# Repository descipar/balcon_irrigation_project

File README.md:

# Balcony Irrigation Project

Automatische Balkonbewässerung: kapazitive Bodenfeuchtesensoren messen die Erde,
kleine 5V-Pumpen gießen bei Bedarf nach.

> **Status:** Version 1 (Arduino Uno, Breadboard) hat funktioniert, hatte aber Bugs
> und war wenig "intelligent". Version 2 (ESP32 + eigene Platine + ESPHome/Home Assistant)
> ist in Planung – siehe [`docs/`](docs/).

## Repository-Struktur

| Pfad | Inhalt |
|---|---|
| `vscode_workspace/BalconIrrigation/` | **Firmware v1** (PlatformIO, Arduino Uno) – letzte lauffähige Version |
| `arduino_workspace/balcon_irrigation/` | Ältere Arduino-IDE-Version (veraltet, gießt nur Topf 1) |
| `arduino_workspace/GraphicsTestExample/` | u8g2-Beispiel aus einem verworfenen Display-Versuch |
| `fritzing_workspace/` | Schaltung v1 (Fritzing): Uno, 5× Sensor, 5× Pumpe über BC337 + 1N4148 |
| `stl/` | 3D-Druckteile: Filmdosen-Behälter (12/20/47 mm), Deckel, Wasserverteiler |
| `docs/` | Analyse von v1, Hardware-Konzept und PCB-Plan für v2 |

## Version 1 (Arduino Uno)

- 2 von 5 Kanälen aktiv: Sensoren an `A0`/`A1`, Pumpen an Pin `10`/`11`
- Alle 30 s messen; Wert > 350 (= trocken) → Pumpe 3 s an
- Bauen/Flashen mit PlatformIO:
  ```sh
  cd vscode_workspace/BalconIrrigation
  pio run -t upload && pio device monitor
  ```

Bekannte Probleme (Details in [`docs/v1-analysis.md`](docs/v1-analysis.md)):
Überwässerungsgefahr ohne Einsickerzeit, keine Hysterese, keine Erkennung
von Sensorfehlern oder leerem Tank, Messwerte gestört durch Pumpen an der gleichen 5V-Versorgung,
`int`-Überlauf bei Wartezeiten > 32767 ms.

## Version 2 (geplant)

- **ESP32** statt Uno – WLAN, NTP-Zeit, OTA-Updates
- **Eigene Platine**, gefertigt und bestückt bei JLCPCB (KiCad)
- 5 Kanäle, Logic-Level-MOSFETs für 5V-Pumpen, separate Pumpenversorgung
- **ESPHome + Home Assistant** für Logik, Verlauf und Benachrichtigungen

Siehe:
- [`docs/v1-analysis.md`](docs/v1-analysis.md) – Bugs & Schwachstellen von v1
- [`docs/v2-hardware.md`](docs/v2-hardware.md) – ESP32-Konzept, Pumpenansteuerung, Pinbelegung
- [`docs/v2-pcb.md`](docs/v2-pcb.md) – PCB-Plan und Toolchain (KiCad auf `serviceplasma`)

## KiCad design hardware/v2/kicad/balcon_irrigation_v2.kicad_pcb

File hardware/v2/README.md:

# Hardware v2 – Steuerplatine

| Datei | Inhalt |
|---|---|
| `gen_schematic.py` | Erzeugt den Schaltplan (die Schaltung ist in `build()` definiert) |
| `kicad/balcon_irrigation_v2.kicad_sch` | Generierter KiCad-9-Schaltplan (A3, 1 Blatt) |
| `kicad/balcon_irrigation_v2.kicad_pro` | KiCad-Projekt |
| `kicad/balcon_irrigation_v2.pdf` | Schaltplan als PDF |
| `gen_layout.py` | Erzeugt und routet die Platine (Platzierung in `placement()`) |
| `kicad/balcon_irrigation_v2.kicad_pcb` | Platine, 100 × 100 mm, 2 Lagen |
| `kicad/balcon_irrigation_v2_top.pdf` / `_bottom.pdf` | Ober- und Unterseite als PDF |

Der Schaltplan wird **nicht von Hand editiert**, sondern neu generiert:

```sh
python3 gen_schematic.py kicad                                    # braucht KiCad-9-Symbolbibliotheken
kicad-cli sch erc --severity-all kicad/balcon_irrigation_v2.kicad_sch
kicad-cli sch export pdf kicad/balcon_irrigation_v2.kicad_sch
```

Die Bibliotheken liegen standardmäßig unter `/usr/share/kicad`, ein anderer Ort geht über `KICAD_SHARE=...`.
Die UUIDs sind deterministisch, deshalb erzeugt derselbe Code mit denselben Bibliotheken (9.0.2) eine byte-identische Datei.
Die Verbindungen laufen über Netz-Labels und Power-Symbole an jedem Pin, nicht über gezeichnete Leitungen.

## Layout

```sh
python3 gen_layout.py kicad/balcon_irrigation_v2.kicad_sch     # ~2 min, braucht pcbnew + Freerouting
kicad-cli pcb drc --schematic-parity kicad/balcon_irrigation_v2.kicad_pcb
```

Ablauf des Skripts:
1. Netzliste aus dem Schaltplan exportieren.
2. Footprints platzieren.
3. Umriss, Bestückungsdruck und Sperrfläche unter der Antenne anlegen.
4. Leiterbahnen mit Freerouting verlegen.
5. Erst danach die GND-Flächen auf beiden Lagen gießen.

Netzklassen: `Power` (+5V, VIN, PUMPx_N) 0,8 mm, `Ground` 0,5 mm, sonst 0,25 mm.
Freerouting liefert bei jedem Lauf ein etwas anderes Ergebnis.
Das eingecheckte `.kicad_pcb` ist der geprüfte Stand.

Platzierung:
- **Links:** Versorgung (Hohlbuchse, Schraubklemme, Sicherung, Verpolschutz, Elko)
- **Oben:** Sensor-, Tank- und I²C-Buchsen
- **Mitte:** DevKit, Antenne rechts über dem Platinenrand, USB links
- **Unten:** 5 Pumpenklemmen mit Treibern
- **Rechts:** Erweiterungsleiste
- **Ecken:** 4 × M3-Bohrungen

## Schaltung

**Versorgung:** 5 V über Hohlbuchse oder Schraubklemme, dann PTC-Sicherung (2 A),
dann Verpolschutz (AO3401A, P-MOSFET high-side), dann `+5V`.
Dazu ein Pufferelko 1000 µF und 100 nF.
`+5V` speist die Pumpen und den 5V-Pin des DevKits. `+3V3` kommt vom Regler des DevKits.

**ESP32-DevKitC V4:** steckt auf 2× Buchsenleiste 1×19 mit 25,4 mm Reihenabstand.
Die Pinbelegung steht in [`docs/v2-hardware.md`](../../docs/v2-hardware.md).

**Pumpenkanal (5×):**
- GPIO → 100 Ω → Gate AO3400A, mit 10k-Pulldown am Gate
- Low-side-Schaltung
- Schottky SS14 als Freilaufdiode zu `+5V`
- Anschluss über Schraubklemme (`+5V` / `PUMPx_N`)

**Sensorkanal (5×):**
- JST-XH 3-polig (GND / 3V3 / AOUT)
- RC-Tiefpass 1 kΩ + 100 nF vor dem ADC1-Pin

**Peripherie:**
- Tank-Schwimmer (JST-XH 2-polig, 10k-Pull-up, RC-Entprellung) an GPIO39
- I²C (JST-XH 4-polig, GND/3V3/SCL/SDA, 4,7k Pull-ups)
- Status-LED an GPIO27
- Erweiterungsleiste mit GPIO 4/13/16/17
- 4× Montageloch M3

LCSC-Nummern (JLC Basic Parts) sind als Feld `LCSC` hinterlegt.
Für Elko, PTC und Steckverbinder fehlen sie noch.

## Vor dem Layout prüfen

- [ ] **DevKit-Variante:** Reihenabstand und Pinfolge am eigenen Board nachmessen.
  Es gibt viele Klone mit 30 Pins oder anderer Breite.
- [ ] **USB + externe 5 V gleichzeitig:** Prüfen, ob das DevKit eine Diode zwischen USB-5V und dem 5V-Pin hat.
  Sonst beim Flashen über USB das Netzteil abziehen.
- [ ] **Pumpenstrom messen:** Anlauf- und Dauerstrom bestimmen. Davon hängen PTC, Leiterbahnbreite und Netzteil ab.
- [ ] **LCSC-Nummern** und Lagerbestand bei JLCPCB prüfen. Fehlende Teile ergänzen: PTC 1812, Elko, XH-Buchsen, Schraubklemmen.
- [ ] **Sensor-Stecker:** Der DFRobot-Sensor hat am Modul einen PH2.0-Stecker.
  Kabel auf JST-XH umcrimpen oder auf der Platine PH2.0 verwenden.

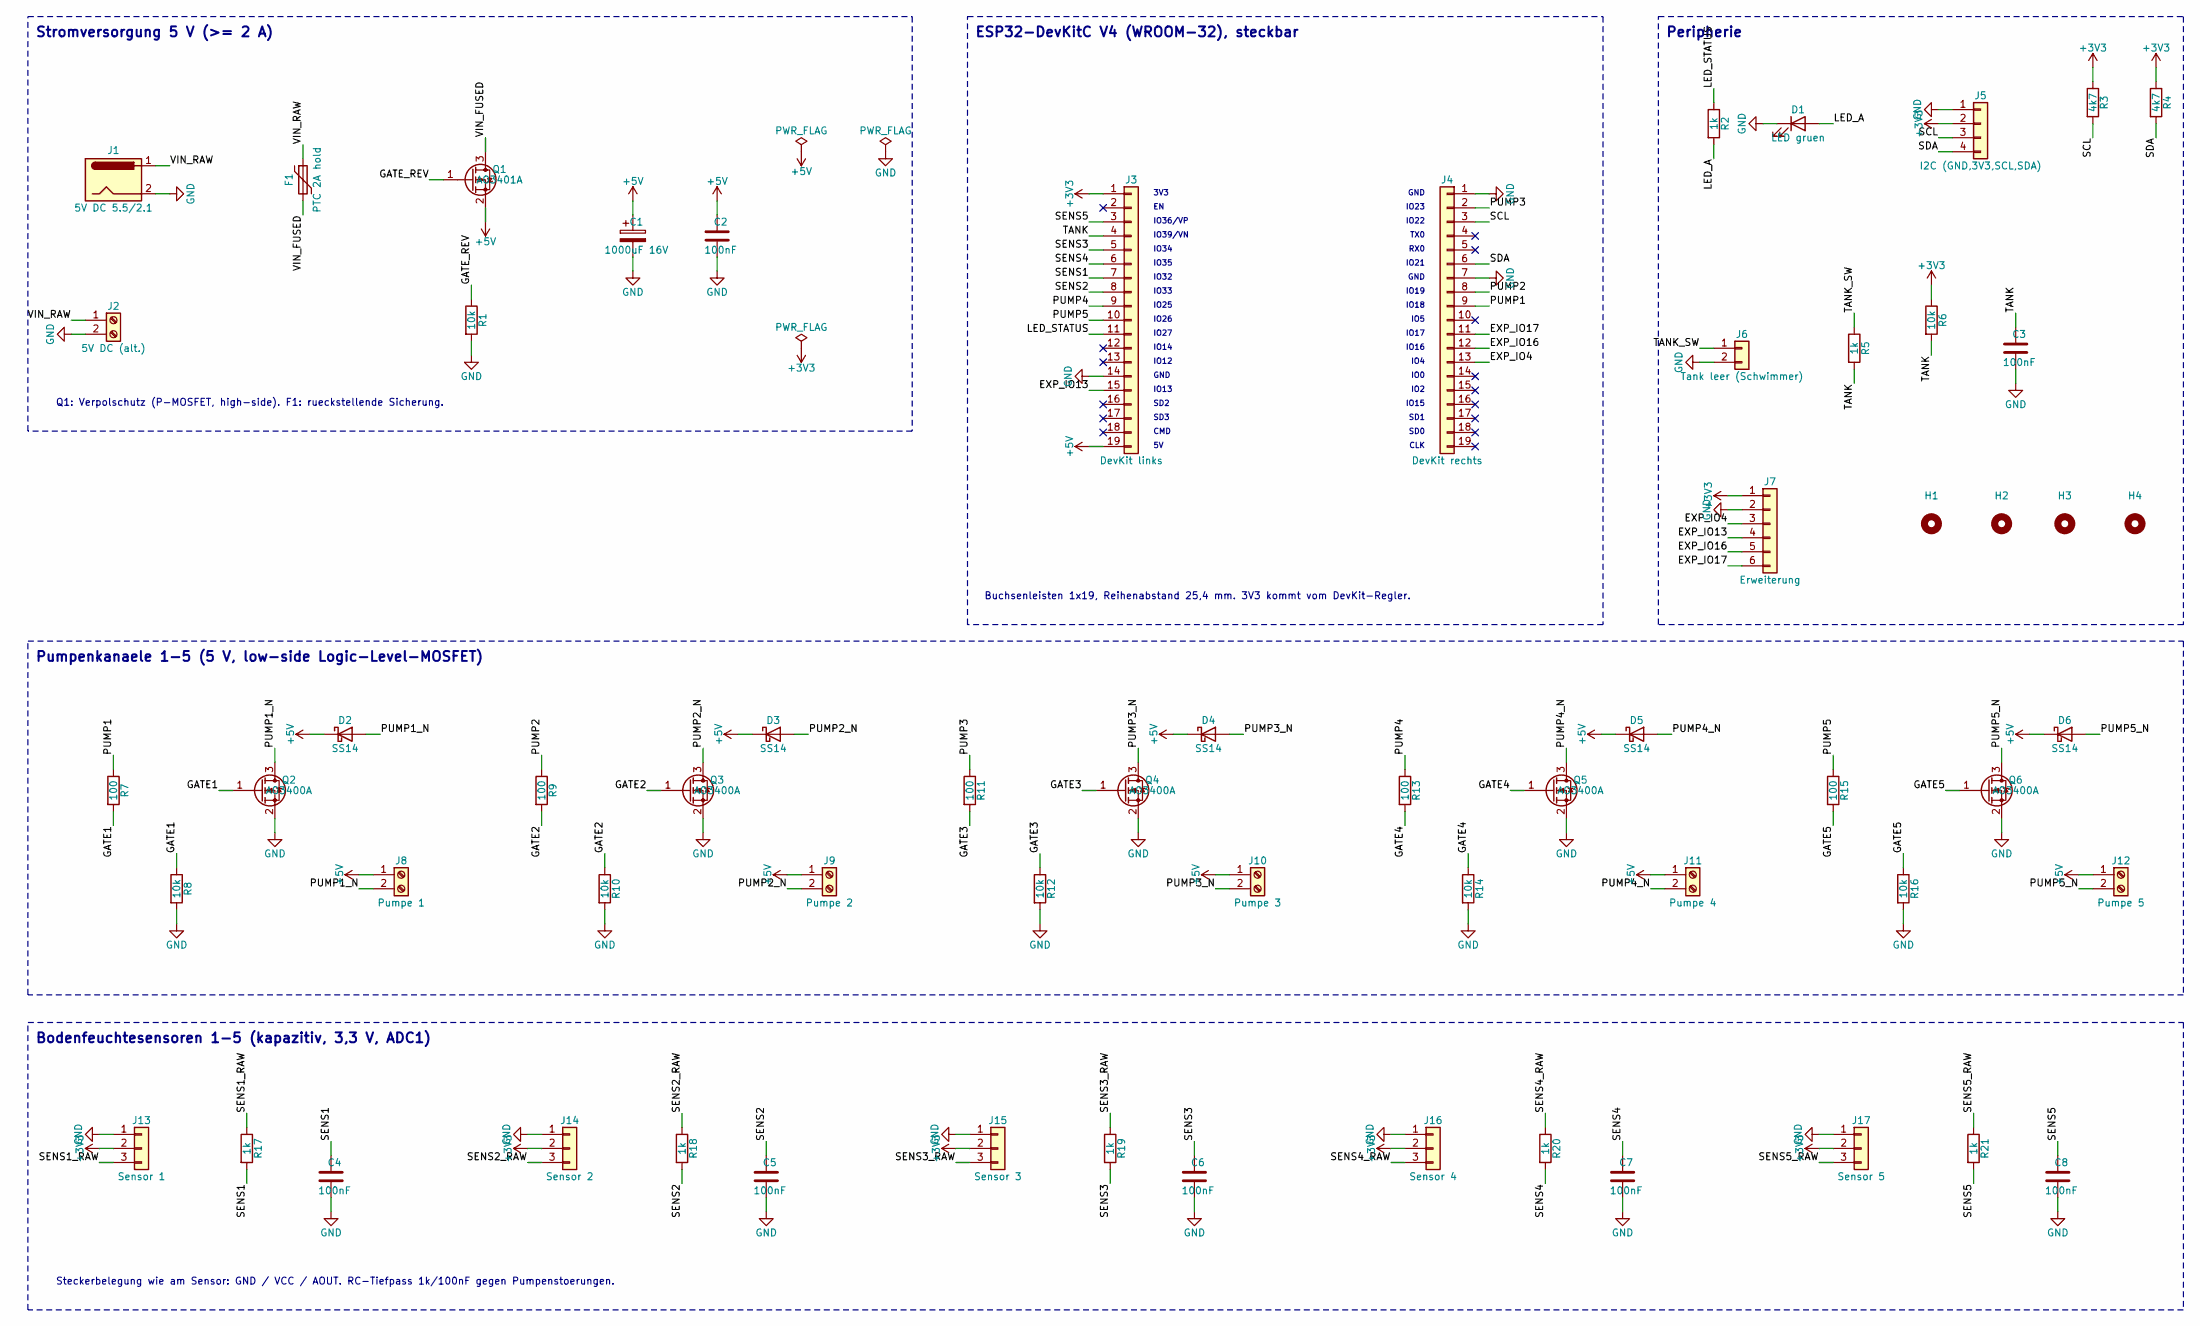
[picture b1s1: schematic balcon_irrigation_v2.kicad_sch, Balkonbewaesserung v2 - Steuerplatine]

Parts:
C1: 1000uF 16V; CP_Radial_D10.0mm_P5.00mm
C2, C3, C4, C5, C6, C7, C8: 100nF; C_0603_1608Metric; LCSC C14663
D1: LED gruen; LED_0603_1608Metric; LCSC C72043
D2, D3, D4, D5, D6: SS14; D_SMA; LCSC C2480
F1: PTC 2A hold; Fuse_1812_4532Metric
H1, H2, H3, H4: M3; MountingHole_3.2mm_M3
J1: 5V DC 5.5/2.1; BarrelJack_Horizontal
J2: 5V DC (alt.); TerminalBlock_Phoenix_MKDS-1,5-2-5.08_1x02_P5.08mm_Horizont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
J3: DevKit links; PinSocket_1x19_P2.54mm_Vertical
J4: DevKit rechts; PinSocket_1x19_P2.54mm_Vertical
J5: I2C (GND,3V3,SCL,SDA); JST_XH_B4B-XH-A_1x04_P2.50mm_Vertical
J6: Tank leer (Schwimmer); JST_XH_B2B-XH-A_1x02_P2.50mm_Vertical
J7: Erweiterung; PinHeader_1x06_P2.54mm_Vertical
J8: Pumpe 1; TerminalBlock_Phoenix_MKDS-1,5-2-5.08_1x02_P5.08mm_Horizont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
J9: Pumpe 2; TerminalBlock_Phoenix_MKDS-1,5-2-5.08_1x02_P5.08mm_Horizont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
J10: Pumpe 3; TerminalBlock_Phoenix_MKDS-1,5-2-5.08_1x02_P5.08mm_Horizont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
J11: Pumpe 4; TerminalBlock_Phoenix_MKDS-1,5-2-5.08_1x02_P5.08mm_Horizont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
J12: Pumpe 5; TerminalBlock_Phoenix_MKDS-1,5-2-5.08_1x02_P5.08mm_Horizont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
J13: Sensor 1; JST_XH_B3B-XH-A_1x03_P2.50mm_Vertical
J14: Sensor 2; JST_XH_B3B-XH-A_1x03_P2.50mm_Vertical
J15: Sensor 3; JST_XH_B3B-XH-A_1x03_P2.50mm_Vertical
J16: Sensor 4; JST_XH_B3B-XH-A_1x03_P2.50mm_Vertical
J17: Sensor 5; JST_XH_B3B-XH-A_1x03_P2.50mm_Vertical
Q1: AO3401A; SOT-23; LCSC C15127
Q2, Q3, Q4, Q5, Q6: AO3400A; SOT-23; LCSC C20917
R1, R6, R8, R10, R12, R14, R16: 10k; R_0603_1608Metric; LCSC C25804
R2, R5, R17, R18, R19, R20, R21: 1k; R_0603_1608Metric; LCSC C21190
R3, R4: 4k7; R_0603_1608Metric; LCSC C23162
R7, R9, R11, R13, R15: 100; R_0603_1608Metric; LCSC C22775

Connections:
+3V3: J3.1, J5.2, J7.1, J13.2, J14.2, J15.2, J16.2, J17.2, R3.1, R4.1, R6.1
+5V: C1.1, C2.1, D2.1 (K), D3.1 (K), D4.1 (K), D5.1 (K), D6.1 (K), J3.19, J8.1, J9.1, J10.1, J11.1, J12.1, Q1.2 (S)
/EXP_IO4: J4.13, J7.3
/EXP_IO13: J3.15, J7.4
/EXP_IO16: J4.12, J7.5
/EXP_IO17: J4.11, J7.6
/GATE1: Q2.1 (G), R7.2, R8.1
/GATE2: Q3.1 (G), R9.2, R10.1
/GATE3: Q4.1 (G), R11.2, R12.1
/GATE4: Q5.1 (G), R13.2, R14.1
/GATE5: Q6.1 (G), R15.2, R16.1
/GATE_REV: Q1.1 (G), R1.1
/LED_A: D1.2 (A), R2.2
/LED_STATUS: J3.11, R2.1
/PUMP1: J4.9, R7.1
/PUMP1_N: D2.2 (A), J8.2, Q2.3 (D)
/PUMP2: J4.8, R9.1
/PUMP2_N: D3.2 (A), J9.2, Q3.3 (D)
/PUMP3: J4.2, R11.1
/PUMP3_N: D4.2 (A), J10.2, Q4.3 (D)
/PUMP4: J3.9, R13.1
/PUMP4_N: D5.2 (A), J11.2, Q5.3 (D)
/PUMP5: J3.10, R15.1
/PUMP5_N: D6.2 (A), J12.2, Q6.3 (D)
/SCL: J4.3, J5.3, R3.2
/SDA: J4.6, J5.4, R4.2
/SENS1: C4.1, J3.7, R17.2
/SENS1_RAW: J13.3, R17.1
/SENS2: C5.1, J3.8, R18.2
/SENS2_RAW: J14.3, R18.1
/SENS3: C6.1, J3.5, R19.2
/SENS3_RAW: J15.3, R19.1
/SENS4: C7.1, J3.6, R20.2
/SENS4_RAW: J16.3, R20.1
/SENS5: C8.1, J3.3, R21.2
/SENS5_RAW: J17.3, R21.1
/TANK: C3.1, J3.4, R5.2, R6.2
/TANK_SW: J6.1, R5.1
/VIN_FUSED: F1.2, Q1.3 (D)
/VIN_RAW: F1.1, J1.1, J2.1
GND: C1.2, C2.2, C3.2, C4.2, C5.2, C6.2, C7.2, C8.2, D1.1 (K), J1.2, J2.2, J3.14, J4.1, J4.7, J5.1, J6.2, J7.2, J13.1, J14.1, J15.1, J16.1, J17.1, Q2.2 (S), Q3.2 (S), Q4.2 (S), Q5.2 (S), Q6.2 (S), R1.2, R8.2, R10.2, R12.2, R14.2, R16.2

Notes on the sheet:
Stromversorgung 5 V (>= 2 A)
Q1: Verpolschutz (P-MOSFET, high-side). F1: rueckstellende Sicherung.
ESP32-DevKitC V4 (WROOM-32), steckbar
3V3
IO36/VP
IO39/VN
IO34
IO35
IO32
IO33
IO25
IO26
IO27
IO14
IO12
GND
IO13
SD2
SD3
CMD
IO23
IO22
TX0
RX0
IO21
IO19
IO18
IO5
IO17
IO16
IO4
IO0
IO2
IO15
SD1
SD0
CLK
Buchsenleisten 1x19, Reihenabstand 25,4 mm. 3V3 kommt vom DevKit-Regler.
Peripherie
Pumpenkanaele 1-5 (5 V, low-side Logic-Level-MOSFET)

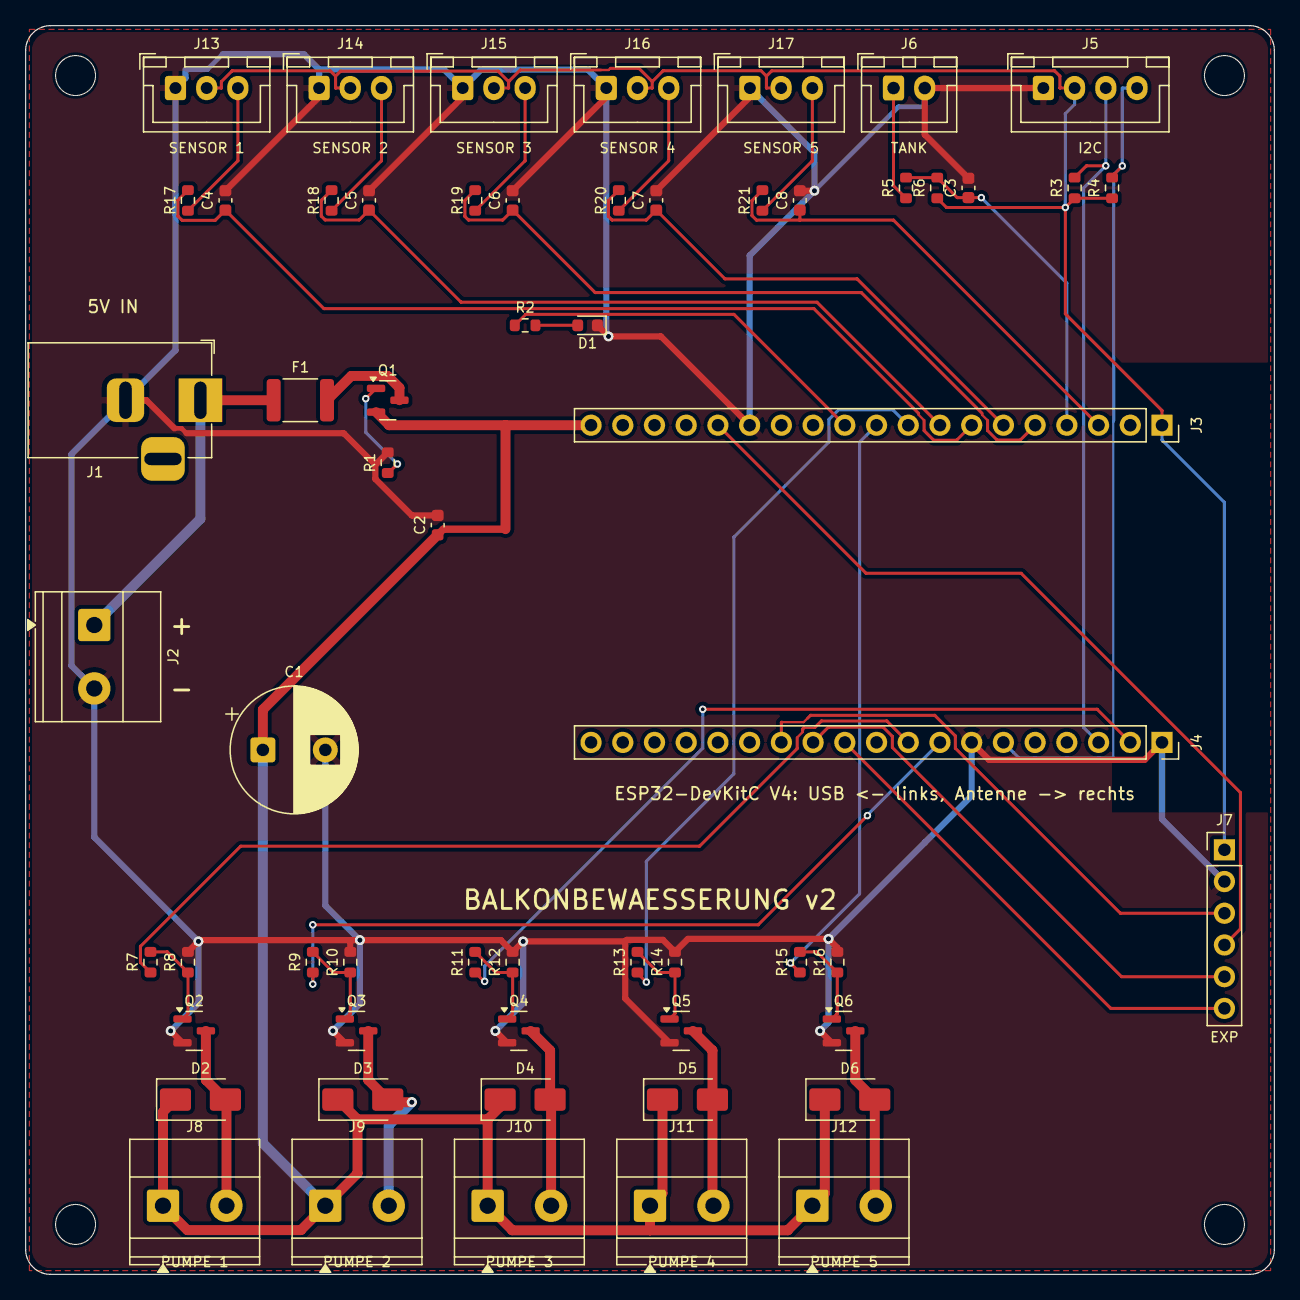
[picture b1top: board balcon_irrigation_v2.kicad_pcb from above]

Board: 2 copper layers, 100.0 x 100.0 mm, 63 parts (0 on the bottom side), 41 nets.

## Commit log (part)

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2020-09-13 breadboard complete
2020-09-13 +
    first try
2020-09-13 another canister
2020-09-13 missing stls
2020-09-15 arduinio sketch initial
2020-09-21 adjusted for soil and tomate
2020-09-21 add comment
2020-09-23 renaming and comments. not done yet
2020-09-24 first try with vs code
2020-09-25 trying to add display to code
2020-09-27 display entfernen
2020-09-27 removed lib depend for version without display
2020-09-27 error searching
2020-09-27 damn error searching
2020-09-28 not working with not enough waiting time
2020-09-30 time wating
2020-09-30 pumping time back to 3000
2020-10-10 testing for sensor values
2022-05-28 Create README.md
    as suggested by github
